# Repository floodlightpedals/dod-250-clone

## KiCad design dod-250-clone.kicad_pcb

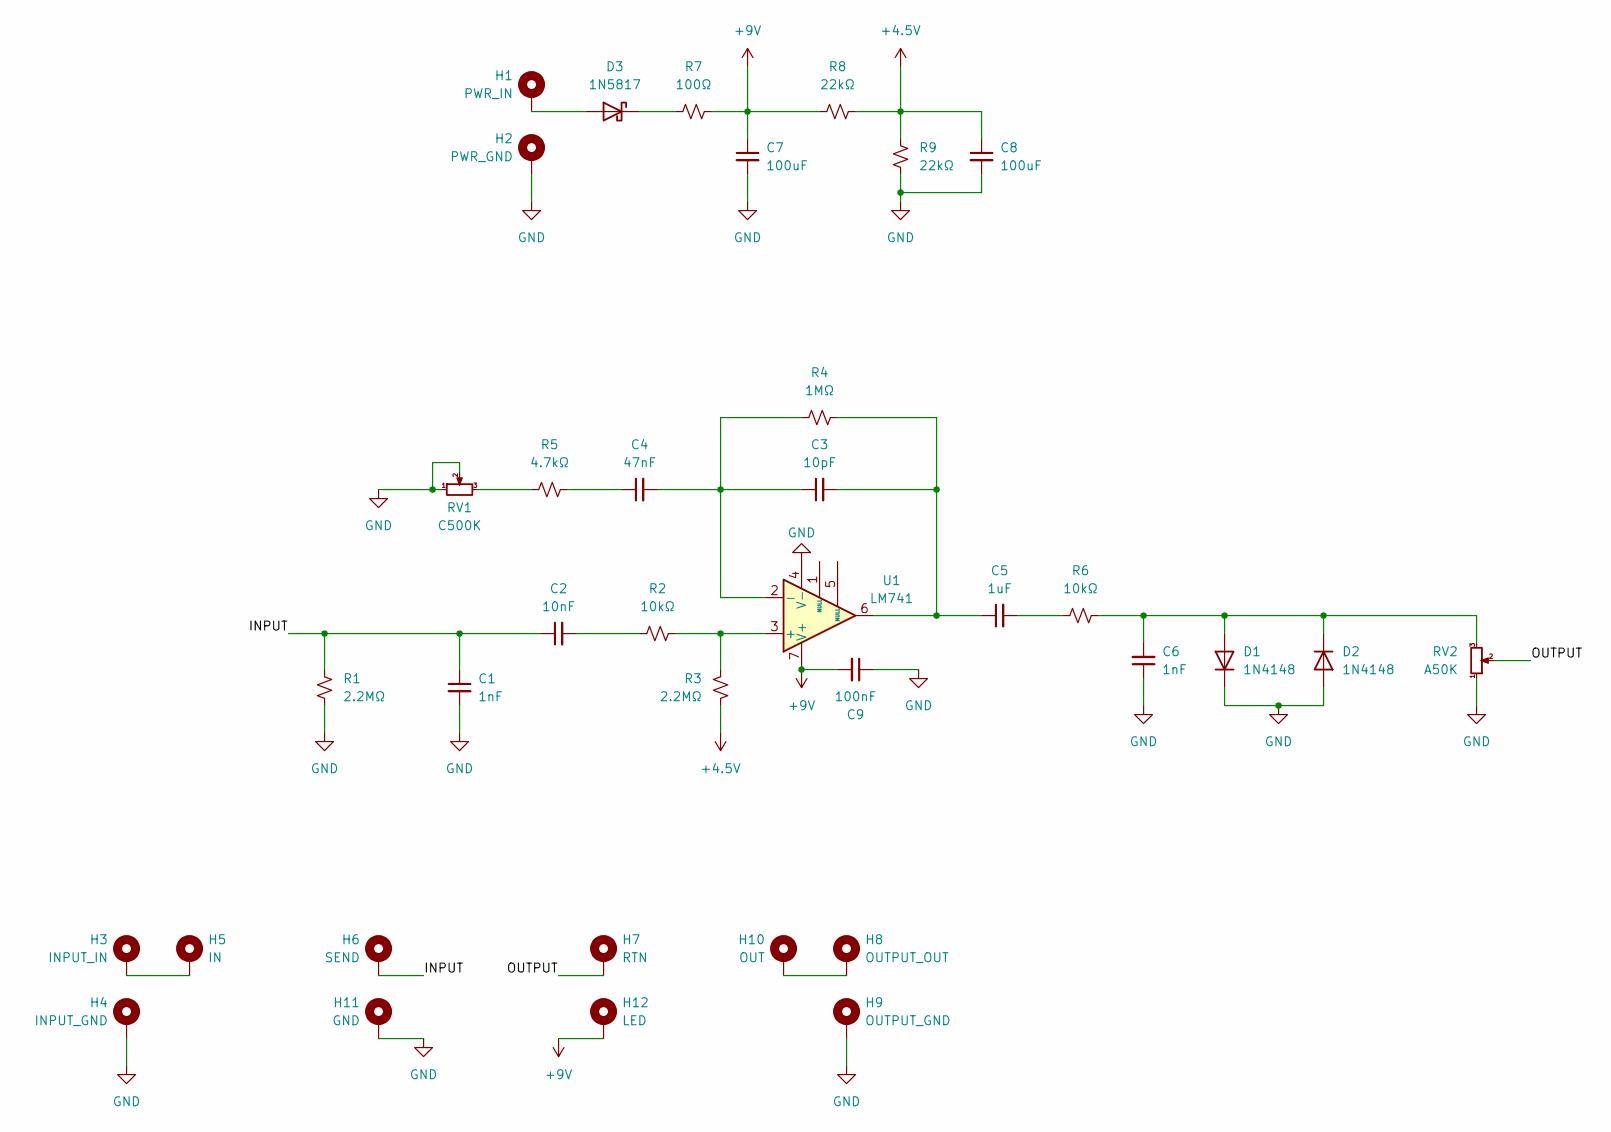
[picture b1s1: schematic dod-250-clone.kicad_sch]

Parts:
C1, C6: 1nF; C_Rect_L7.2mm_W2.5mm_P5.00mm_FKS2_FKP2_MKS2_MKP2
C2: 10nF; C_Rect_L7.2mm_W2.5mm_P5.00mm_FKS2_FKP2_MKS2_MKP2
C3: 10pF; C_Disc_D3.8mm_W2.6mm_P2.50mm
C4: 47nF; C_Rect_L7.2mm_W2.5mm_P5.00mm_FKS2_FKP2_MKS2_MKP2
C5: 1uF; C_Rect_L7.2mm_W2.5mm_P5.00mm_FKS2_FKP2_MKS2_MKP2
C7, C8: 100uF; CP_Radial_D6.3mm_P2.50mm
C9: 100nF; C_Rect_L7.2mm_W2.5mm_P5.00mm_FKS2_FKP2_MKS2_MKP2
D1, D2: 1N4148; D_DO-35_SOD27_P7.62mm_Horizontal
D3: 1N5817; D_DO-41_SOD81_P10.16mm_Horizontal
H1: PWR_IN; MountingHole_2.2mm_M2_DIN965_Pad_TopBottom
H2: PWR_GND; MountingHole_2.2mm_M2_DIN965_Pad_TopBottom
H3: INPUT_IN; MountingHole_2.2mm_M2_DIN965_Pad_TopBottom
H4: INPUT_GND; MountingHole_2.2mm_M2_DIN965_Pad_TopBottom
H5: IN; MountingHole_2.2mm_M2_DIN965_Pad_TopBottom
H6: SEND; MountingHole_2.2mm_M2_DIN965_Pad_TopBottom
H7: RTN; MountingHole_2.2mm_M2_DIN965_Pad_TopBottom
H8: OUTPUT_OUT; MountingHole_2.2mm_M2_DIN965_Pad_TopBottom
H9: OUTPUT_GND; MountingHole_2.2mm_M2_DIN965_Pad_TopBottom
H10: OUT; MountingHole_2.2mm_M2_DIN965_Pad_TopBottom
H11: GND; MountingHole_2.2mm_M2_DIN965_Pad_TopBottom
H12: LED; MountingHole_2.2mm_M2_DIN965_Pad_TopBottom
R1, R3: 2.2MΩ; R_Axial_DIN0207_L6.3mm_D2.5mm_P7.62mm_Horizontal
R2, R6: 10kΩ; R_Axial_DIN0207_L6.3mm_D2.5mm_P7.62mm_Horizontal
R4: 1MΩ; R_Axial_DIN0207_L6.3mm_D2.5mm_P7.62mm_Horizontal
R5: 4.7kΩ; R_Axial_DIN0207_L6.3mm_D2.5mm_P7.62mm_Horizontal
R7: 100Ω; R_Axial_DIN0207_L6.3mm_D2.5mm_P7.62mm_Horizontal
R8, R9: 22kΩ; R_Axial_DIN0207_L6.3mm_D2.5mm_P7.62mm_Horizontal
RV1: C500K; Alpha_RV16AF-41
RV2: A50K; Alpha_RV16AF-41
U1: LM741; DIP-8_W7.62mm

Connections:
+4.5V: C8.1, R3.2, R8.2, R9.2
+9V: C7.1, C9.2, H12.1, R7.2, R8.1, U1.7 (V+)
/INPUT: C1.1, C2.1, H6.1, R1.1
/OUTPUT: H7.1, RV2.2
GND: C1.2, C6.1, C7.2, C8.2, C9.1, D1.1 (K), D2.2 (A), H2.1, H4.1, H9.1, H11.1, R1.2, R9.1, RV1.1, RV1.2, RV2.1, U1.4 (V-)
unnamed: C2.2, R2.1
unnamed: C3.2, C5.1, R4.2, U1.6
unnamed: C4.1, R5.2
unnamed: C5.2, R6.1
unnamed: C6.2, D1.2 (A), D2.1 (K), R6.2, RV2.3
unnamed: D3.2 (A), H1.1
unnamed: D3.1 (K), R7.1
unnamed: H3.1, H5.1
unnamed: H8.1, H10.1
unnamed: R5.1, RV1.3
unnamed: R2.2, R3.1, U1.3 (+)
unnamed: C3.1, C4.2, R4.1, U1.2 (-)

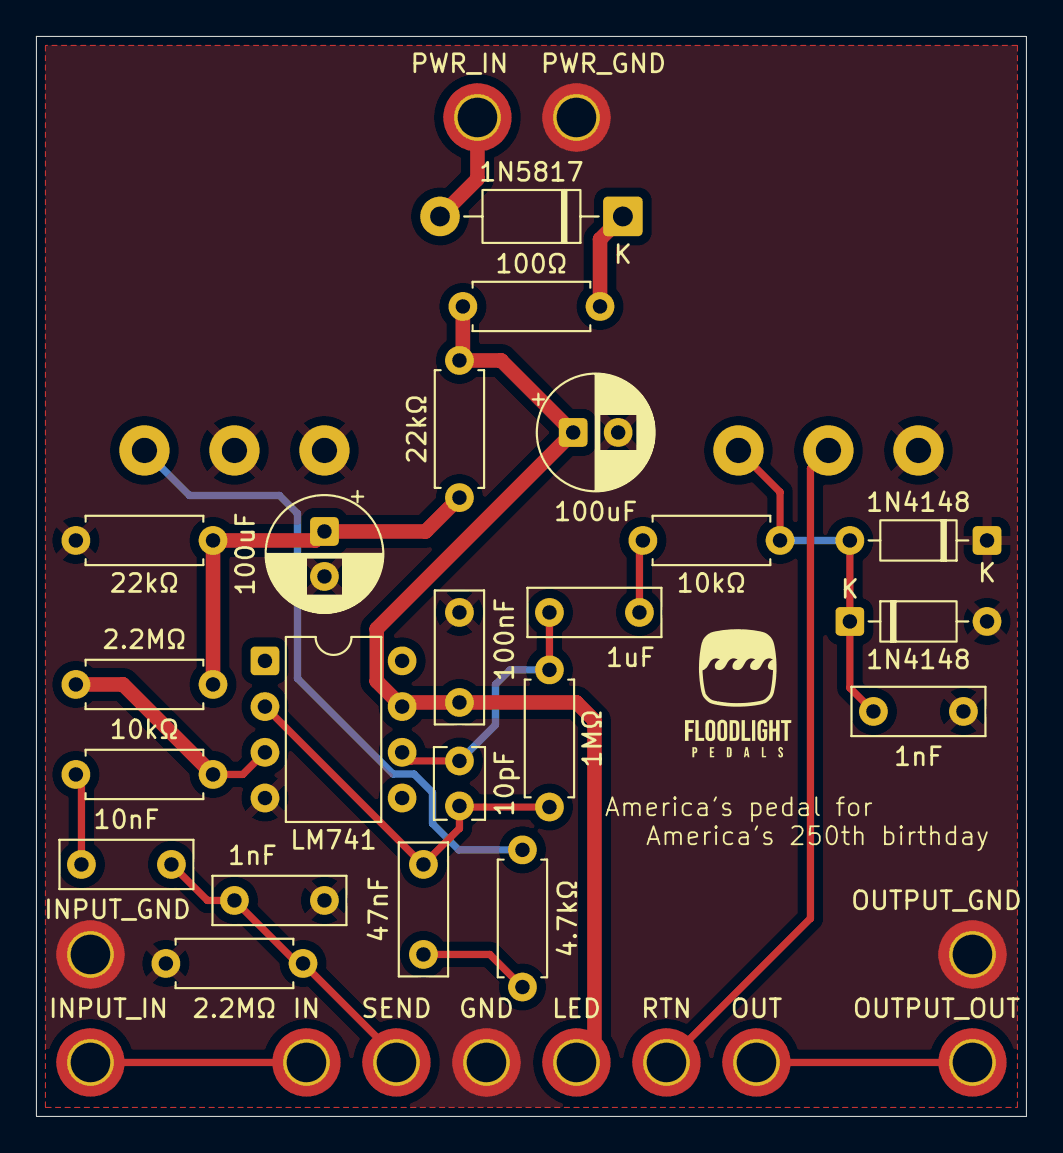
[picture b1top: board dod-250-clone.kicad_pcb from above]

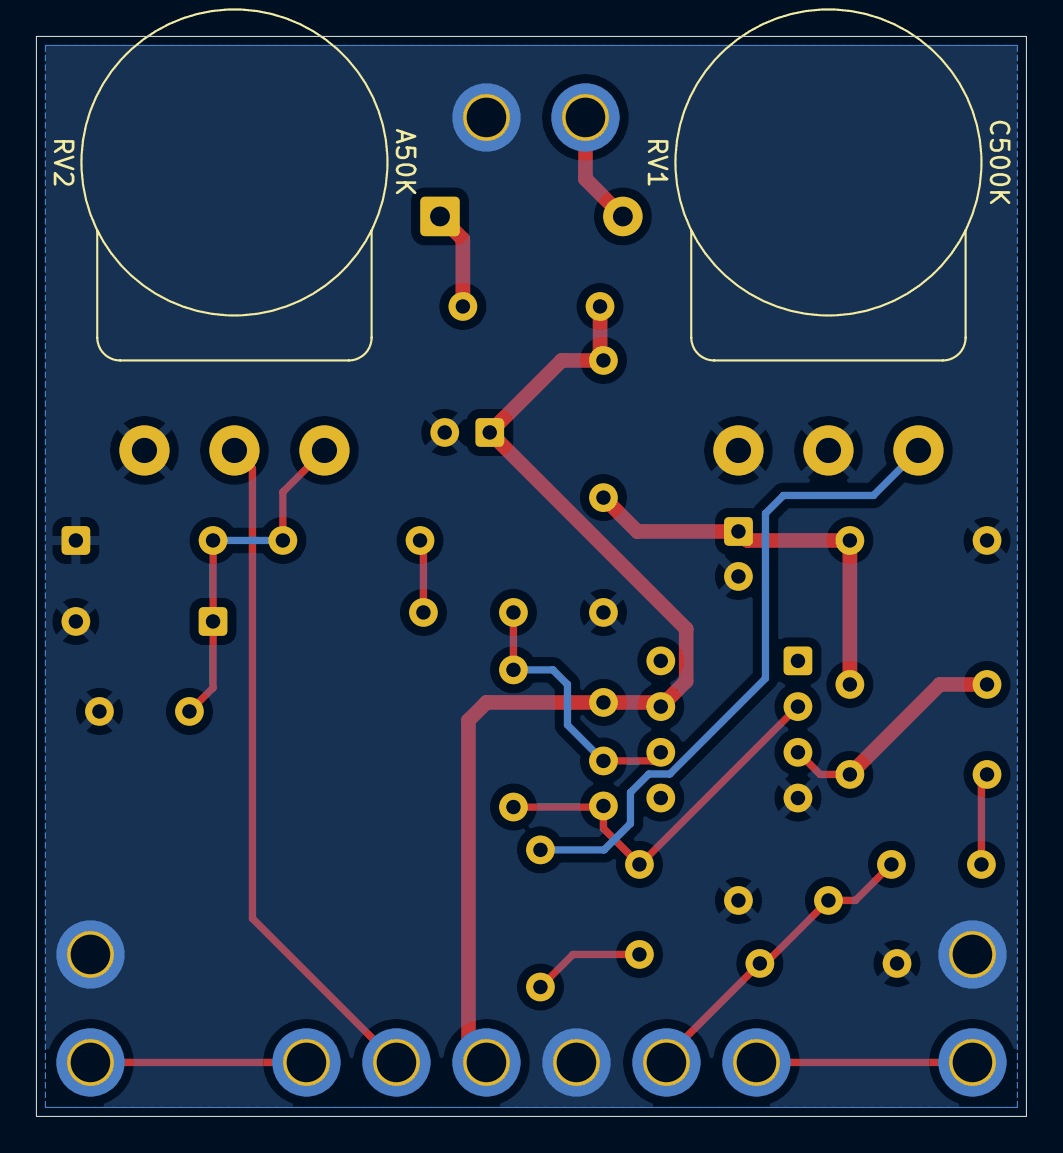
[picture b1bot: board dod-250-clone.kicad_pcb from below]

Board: 2 copper layers, 55.0 x 60.0 mm, 36 parts (2 on the bottom side), 17 nets.
